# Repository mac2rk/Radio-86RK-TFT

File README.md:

# Connecting Radio-86RK to TFT display panel

Connecting TFT display with 24bit RGB parallel interface to Intel i8275 CRTC

## Introduction

For many home computers from 1980s, TV was the only display available, and [Radio-86RK](https://github.com/mac2rk/Radio-86RK-SRAM) is no exception. Back then, it made total sense, but today, TVs with composite video input gradualy disappear, and being tethered to one when playing with a 8-bit retro computer is, well, too much retro.

Turns out, small TFT display panels are now available, affordable, and can be connected to Radio-86RK relatively easily.

This project is a hardware interface between Intel i8275 CRT controller and a 480x272 pixel TFT panel [ER-TFT050-2](https://www.buydisplay.com/download/manual/ER-TFT050-2_Datasheet.pdf) with the ILI6482 controller onboard. This inteface board supports 4-bit (IRGB) color, although color is not implemented in [Radio-86RK](https://github.com/mac2rk/Radio-86RK-SRAM). The interface has been shown to work with a Sinclair ZX Spectrum clone (Harlequin), too, although it was not explored in any detail.

## Schematic

[Schematic](Eagle/rk86_tft-schematic.pdf)

In the schematic, IC3 converts logic levels from 5V of [Radio-86RK](https://github.com/mac2rk/Radio-86RK-SRAM) to 3.3V required by the TFT panel; IC6 feeds the TFT panel's backlight (a string of white LEDs) with constant current; IC7 provides I2C interface for the resistive touchscreen; IC8 regulates +5V power supply down to +3.3V. Q1 provides protection against wrong power supply polarity, Q2 and Q3 convert I2C voltage levels.

IC4 and IC5.1 form the brown color `#AA5500`instead of unsightly "dark yellow" `#AAAA00` for IRGB=0b0110, forming the standard CGA palette:

4-bit IRGB code | 24-bit color | Color
--------------- | ------------ | -----
0b0000          | `#000000`    | Black
0b0001          | `#0000AA`    | Blue
0b0010          | `#00AA00`    | Green
0b0011          | `#00AAAA`    | Cyan
0b0100          | `#AA0000`    | Red
0b0101          | `#AA00AA`    | Magenta
0b0110          | `#AA5500`    | Brown
0b0111          | `#AAAAAA`    | Light gray
0b1000          | `#555555`    | Dark gray
0b1001          | `#5555FF`    | Bright blue
0b1010          | `#55FF55`    | Bright green
0b1011          | `#55FFFF`    | Bright cyan
0b1100          | `#FF5555`    | Bright Red
0b1101          | `#FF55FF`    | Bright magenta
0b1110          | `#FFFF55`    | Yellow
0b1111          | `#FFFFFF`    | White

IC2's function is specific to [Radio-86RK](https://github.com/mac2rk/Radio-86RK-SRAM). In Radio-86RK, the i8275 CRTC forms a raster with 300 horizontal lines, although top 30 and bottom 20 are not used for display. The TFT panel, however, is only 272 pixels tall, so 300-20-272=8 lines at the bottom  of the display area do not fit. Thankfully, the TFT panel ignores HRTC pulses and is completely controlled by VRTC and DEN (Data ENable) signals. IC2 suppresses DEN for the top 16 lines, thus fitting the full display area into the panel without reprogramming the CRTC, ensuring compatibility with existing software.

## PCB layout

[PCB layout](Eagle/rk86_tft-board.pdf)

## Bill of Materials

Name              | Part      | Value       | Package | Quantity
----------------- | --------- | ----------- | ------- | --------
LCD1              | LCD panel | ER-TFT050-2 |         | 1
LCD1              | 30-way 0.5mm FPC connector, top contact |  | Molex 54014-4031 | 1
IC1               | Logic IC  | 74HC04PW    | TSSOP14 | 1
IC2               | Logic IC  | 74HC161PW   | TSSOP16 | 1
IC3               | Logic IC  | 74LVC8T245DBQR | TSSOP24 | 1
IC4               | Logic IC  | QS3VH253PAG | TSSOP16 | 1
IC5               | Logic IC  | 74HC08PW    | TSSOP14 | 1
IC6               | Backlight Driver IC | AP3019AKTR | SOT23-6 | 1
IC7               | Touchscreen Controller IC | TSC2007PW | TSSOP16 | 1
IC8               | Voltage Reg IC | MCP1700T-3302E/TT | SOT23-3 | 1
Q1                | Pch MOSFET | FDC658P    | SOT23-6 | 1
Q2,Q3             | Nch MOSFET | BSS138     | SOT23-3 | 2
R1,R2,R4..R7      | Resistor  | 10kOhm | 0805    | 6
R3                | Resistor  | 5ohm   | 0805    | 1
R8..R13           | Resistor  | 220ohm | 0805    | 6
C1..C6, C11, C13  | Capacitor | 0.1uF  | 0805    | 8
C8, C10, C12, C14 | Capacitor | 10uF   | 0805    | 4
C9                | Capacitor | 0.22uF | 0805    | 1
L1                | Inductor | 22uH    | Coilcraft XTL7030 | 1
CLK,DEN,HRTC,I2C,PWR,VRTC | LED |      | 0805    | 6
JP1         | 0.1" Pin Header |        | 1x10    | 1
I2X1        | 0.1" Pin Header |        | 1x4     | 1

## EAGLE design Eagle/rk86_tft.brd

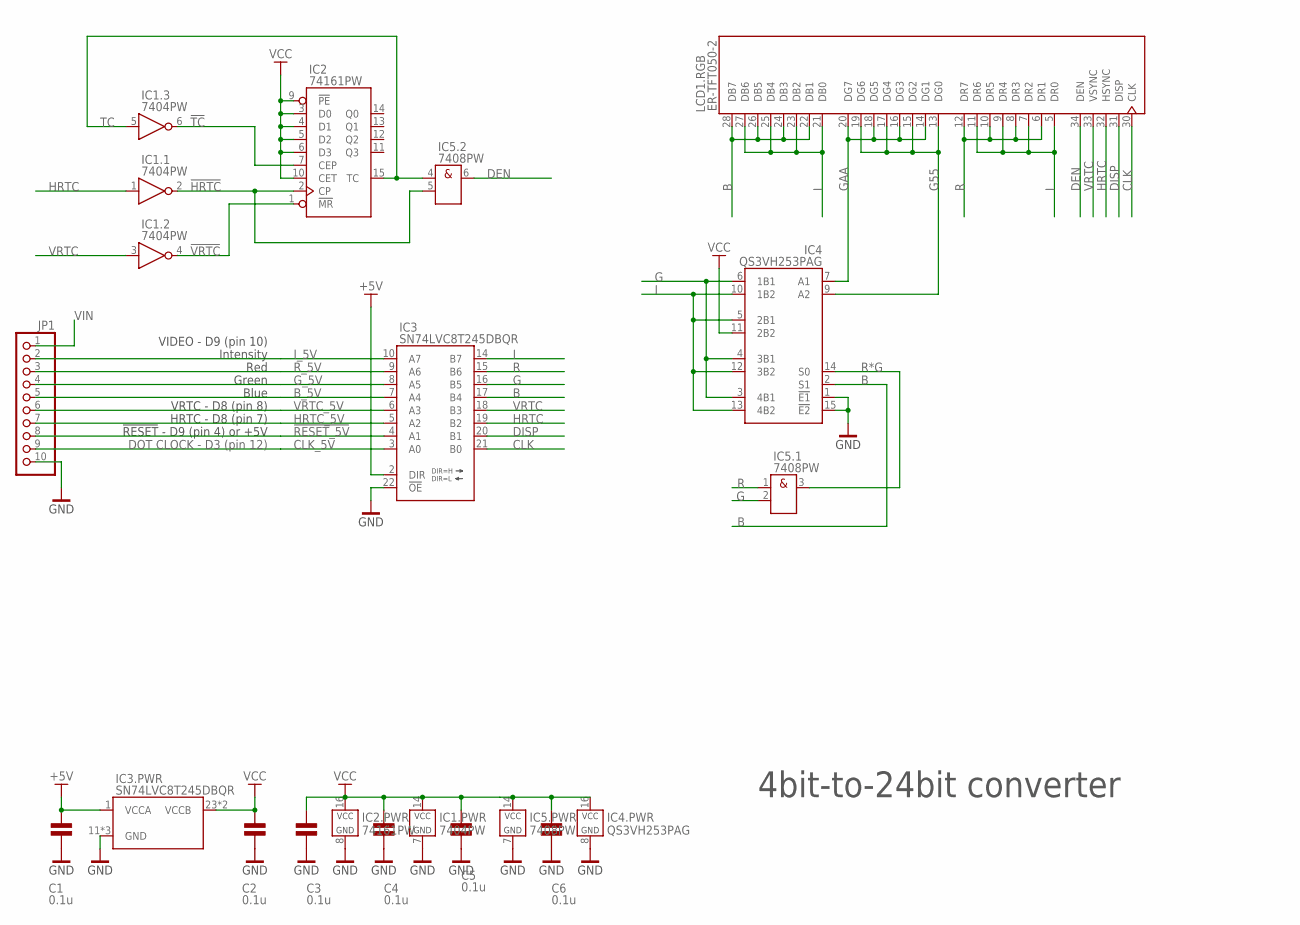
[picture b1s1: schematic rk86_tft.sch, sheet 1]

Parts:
C1, C2, C3, C4, C5, C6: 0.1u; 0805
IC1: 7404PW; TSSOP14_4.4
IC2: 74161PW; TSSOP16_4.4
IC3: SN74LVC8T245DBQR; TI_DBQ24
IC4: QS3VH253PAG; TSSOP16_4.4
IC5: 7408PW; TSSOP14_4.4
JP1: PINHD-1X10/90; 1X10/90
LCD1: ER-TFT050-2; MOLEX_54104-4031

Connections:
!HRTC: IC1.2 (Y), IC2.2 (CP), IC5.5 (B); also elsewhere on the board
!RESET_5V: IC3.4 (A1), JP1.8
!TC: IC1.6 (Y), IC2.7 (CEP)
!VRTC: IC1.4 (Y), IC2.1 (!MR); also elsewhere on the board
+5V: C1.2, IC3.1 (VCCA), IC3.2 (DIR); also elsewhere on the board
B: IC3.17 (B4), IC4.2 (S1), LCD1.22 (DB1), LCD1.24 (DB3), LCD1.26 (DB5), LCD1.28 (DB7)
B_5V: IC3.7 (A4), JP1.5
CLK: IC3.21 (B0), LCD1.30 (CLK); also elsewhere on the board
CLK_5V: IC3.3 (A0), JP1.9
DEN: IC5.6 (Y), LCD1.34 (DEN); also elsewhere on the board
DISP: IC3.20 (B1), LCD1.31 (DISP)
G: IC3.16 (B5), IC4.3 (4B1), IC4.4 (3B1), IC4.6 (1B1), IC5.2 (B)
G55: IC4.9 (A2), LCD1.13 (DG0), LCD1.15 (DG2), LCD1.17 (DG4), LCD1.19 (DG6)
GAA: IC4.7 (A1), LCD1.14 (DG1), LCD1.16 (DG3), LCD1.18 (DG5), LCD1.20 (DG7)
GND: C1.1, C2.1, C3.1, C4.1, C5.1, C6.1, IC1.7 (GND), IC2.8 (GND), IC3.11 (GND), IC3.12 (GND), IC3.13 (GND), IC3.22 (!OE), IC4.1 (!E1), IC4.8 (GND), IC4.15 (!E2), IC5.7 (GND), JP1.10; also elsewhere on the board
G_5V: IC3.8 (A5), JP1.4
HRTC: IC1.1 (A), IC3.19 (B2), LCD1.32 (HSYNC)
HRTC_5V: IC3.5 (A2), JP1.7
I: IC3.14 (B7), IC4.5 (2B1), IC4.10 (1B2), IC4.12 (3B2), IC4.13 (4B2), LCD1.5 (DR0), LCD1.7 (DR2), LCD1.9 (DR4), LCD1.11 (DR6), LCD1.21 (DB0), LCD1.23 (DB2), LCD1.25 (DB4), LCD1.27 (DB6)
I_5V: IC3.10 (A7), JP1.2
R: IC3.15 (B6), IC5.1 (A), LCD1.6 (DR1), LCD1.8 (DR3), LCD1.10 (DR5), LCD1.12 (DR7)
R*G: IC4.14 (S0), IC5.3 (Y)
R_5V: IC3.9 (A6), JP1.3
TC: IC1.5 (A), IC2.15 (TC), IC5.4 (A)
VCC: C2.2, C3.2, C4.2, C5.2, C6.2, IC1.14 (VCC), IC2.3 (D0), IC2.4 (D1), IC2.5 (D2), IC2.6 (D3), IC2.9 (!PE), IC2.10 (CET), IC2.16 (VCC), IC3.23 (VCCB), IC3.24 (VCCB), IC4.11 (2B2), IC4.16 (VCC), IC5.14 (VCC); also elsewhere on the board
VIN: JP1.1; also elsewhere on the board
VRTC: IC1.3 (A), IC3.18 (B3), LCD1.33 (VSYNC)
VRTC_5V: IC3.6 (A3), JP1.6

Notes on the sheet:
4bit-to-24bit converter
VIDEO - D9 (pin 10)
VRTC - D8 (pin 8)
HRTC - D8 (pin 7)
DOT CLOCK - D3 (pin 12)
!RESET! - D9 (pin 4) or +5V
Intensity
Red
Green
Blue

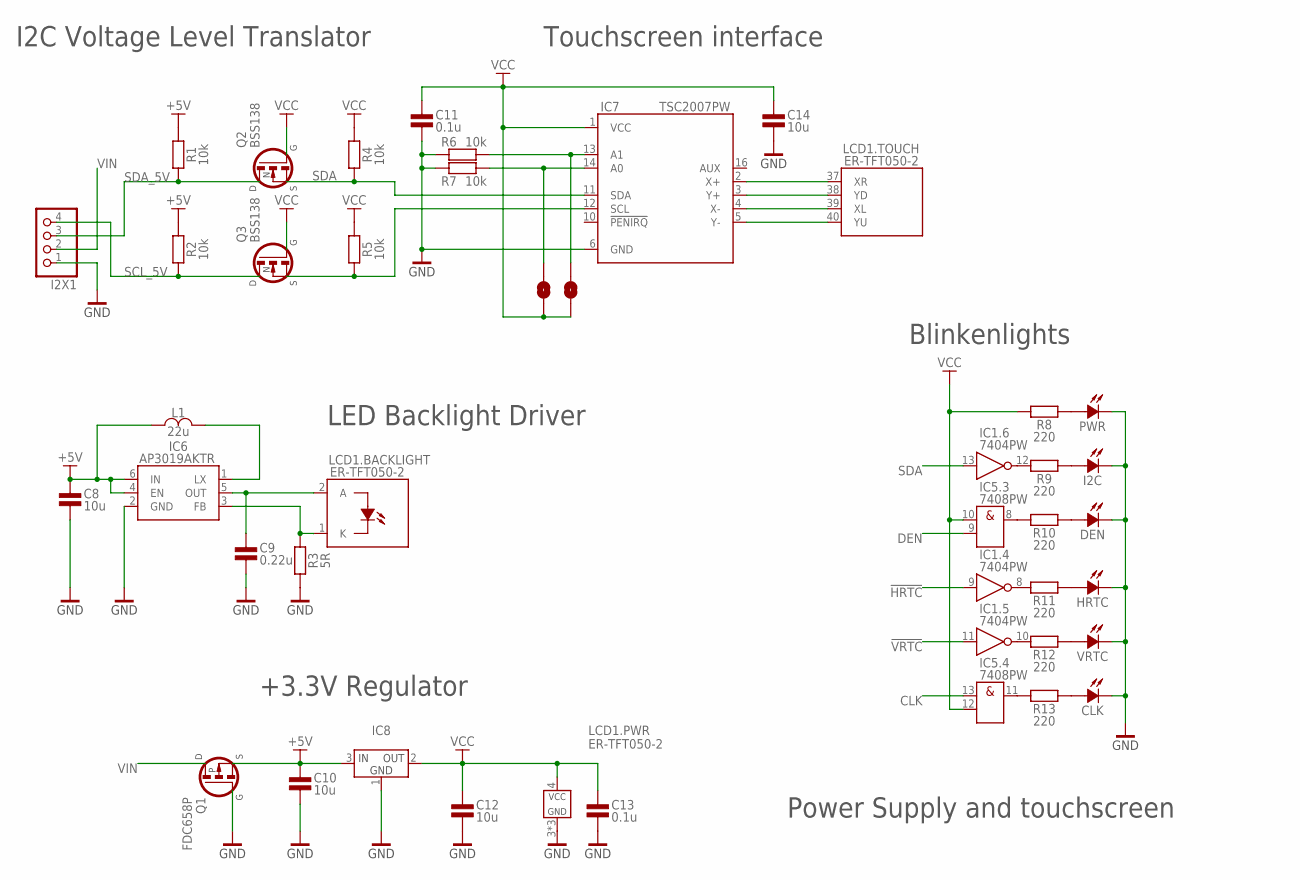
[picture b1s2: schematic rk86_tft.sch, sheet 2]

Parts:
A0, A1: SJ
C8, C10, C12, C14: 10u; 0805
C9: 0.22u; 0805
C11, C13: 0.1u; 0805
CLK: LED0805; 0805POL
DEN: LED0805; 0805POL
HRTC: LED0805; 0805POL
I2C: LED0805; 0805POL
I2X1: PINHD-1X4/90; 1X04/90
IC1: 7404PW; TSSOP14_4.4
IC5: 7408PW; TSSOP14_4.4
IC6: AP3019AKTR; SOT23-6
IC7: TSC2007PW; TSSOP16_4.4
IC8: MCP1700TT; SOT23-3
L1: 22u; COILCRAFT_XTL7030
LCD1: ER-TFT050-2; MOLEX_54104-4031
PWR: LED0805; 0805POL
Q1: FDC658P; SOT23-6
Q2, Q3: BSS138; SOT23-3
R1, R2, R4, R5, R6, R7: 10k; 0805
R3: 5R; 0805
R8, R9, R10, R11, R12, R13: 220; 0805
VRTC: LED0805; 0805POL

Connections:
!HRTC: IC1.9 (A); also elsewhere on the board
!VRTC: IC1.11 (A); also elsewhere on the board
+5V: C8.2, C10.2, IC6.4 (EN), IC6.6 (IN), IC8.3 (IN), L1.1, Q1.4 (S), R1.2, R2.2; also elsewhere on the board
CLK: IC5.13 (A); also elsewhere on the board
DEN: IC5.9 (B); also elsewhere on the board
GND: C8.1, C9.1, C10.1, C11.1, C12.1, C13.1, C14.1, CLK.K, DEN.K, HRTC.K, I2C.K, I2X1.1, IC6.2 (GND), IC7.6 (GND), IC8.1 (GND), LCD1.3 (GND), LCD1.29 (GND), LCD1.36 (GND), PWR.K, Q1.3 (G), R3.1, R6.1, R7.1, VRTC.K; also elsewhere on the board
LEDA: C9.2, IC6.5 (OUT), LCD1.2 (A)
LEDK: IC6.3 (FB), LCD1.1 (K), R3.2
LX: IC6.1 (LX), L1.2
unnamed: IC1.8 (Y), R11.1
unnamed: IC1.10 (Y), R12.1
unnamed: IC1.12 (Y), R9.1
unnamed: IC5.11 (Y), R13.1
unnamed: IC5.8 (Y), R10.1
unnamed: A1.2, IC7.13 (A1), R6.2
unnamed: A0.2, IC7.14 (A0), R7.2
unnamed: I2C.A, R9.2
unnamed: DEN.A, R10.2
unnamed: HRTC.A, R11.2
unnamed: R12.2, VRTC.A
unnamed: IC7.2 (X+), LCD1.37 (XR)
unnamed: IC7.4 (X-), LCD1.39 (XL)
unnamed: IC7.3 (Y+), LCD1.38 (YD)
unnamed: IC7.5 (Y-), LCD1.40 (YU)
unnamed: CLK.A, R13.2
unnamed: PWR.A, R8.2
SCL: IC7.12 (SCL), Q3.2 (S), R5.1
SCL_5V: I2X1.4, Q3.3 (D), R2.1
SDA: IC1.13 (A), IC7.11 (SDA), Q2.2 (S), R4.1
SDA_5V: I2X1.3, Q2.3 (D), R1.1
VCC: A0.1, A1.1, C11.2, C12.2, C13.2, C14.2, IC5.10 (A), IC5.12 (B), IC7.1 (VCC), IC8.2 (OUT), LCD1.4 (VCC), Q2.1 (G), Q3.1 (G), R4.2, R5.2, R8.1; also elsewhere on the board
VIN: I2X1.2, Q1.1 (D), Q1.2 (D), Q1.5 (D), Q1.6 (D); also elsewhere on the board

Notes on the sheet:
I2C Voltage Level Translator
+3.3V Regulator
LED Backlight Driver
Touchscreen interface
Blinkenlights
Power Supply and touchscreen

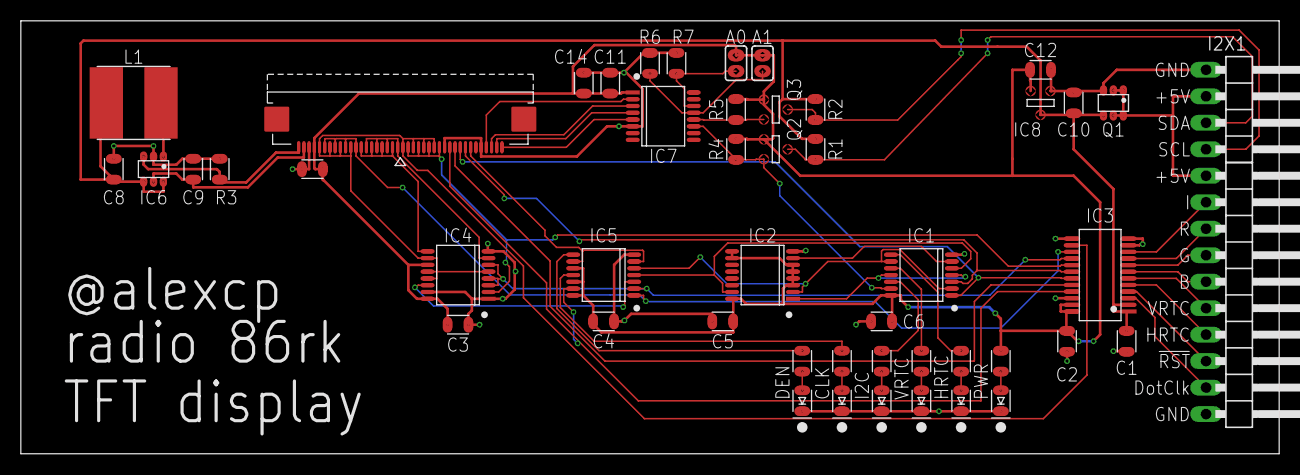
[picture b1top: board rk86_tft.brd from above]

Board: 2 copper layers, 120.7 x 41.5 mm, 49 parts (0 on the bottom side), 52 nets.

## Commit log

2021-09-05 Added gerbers
